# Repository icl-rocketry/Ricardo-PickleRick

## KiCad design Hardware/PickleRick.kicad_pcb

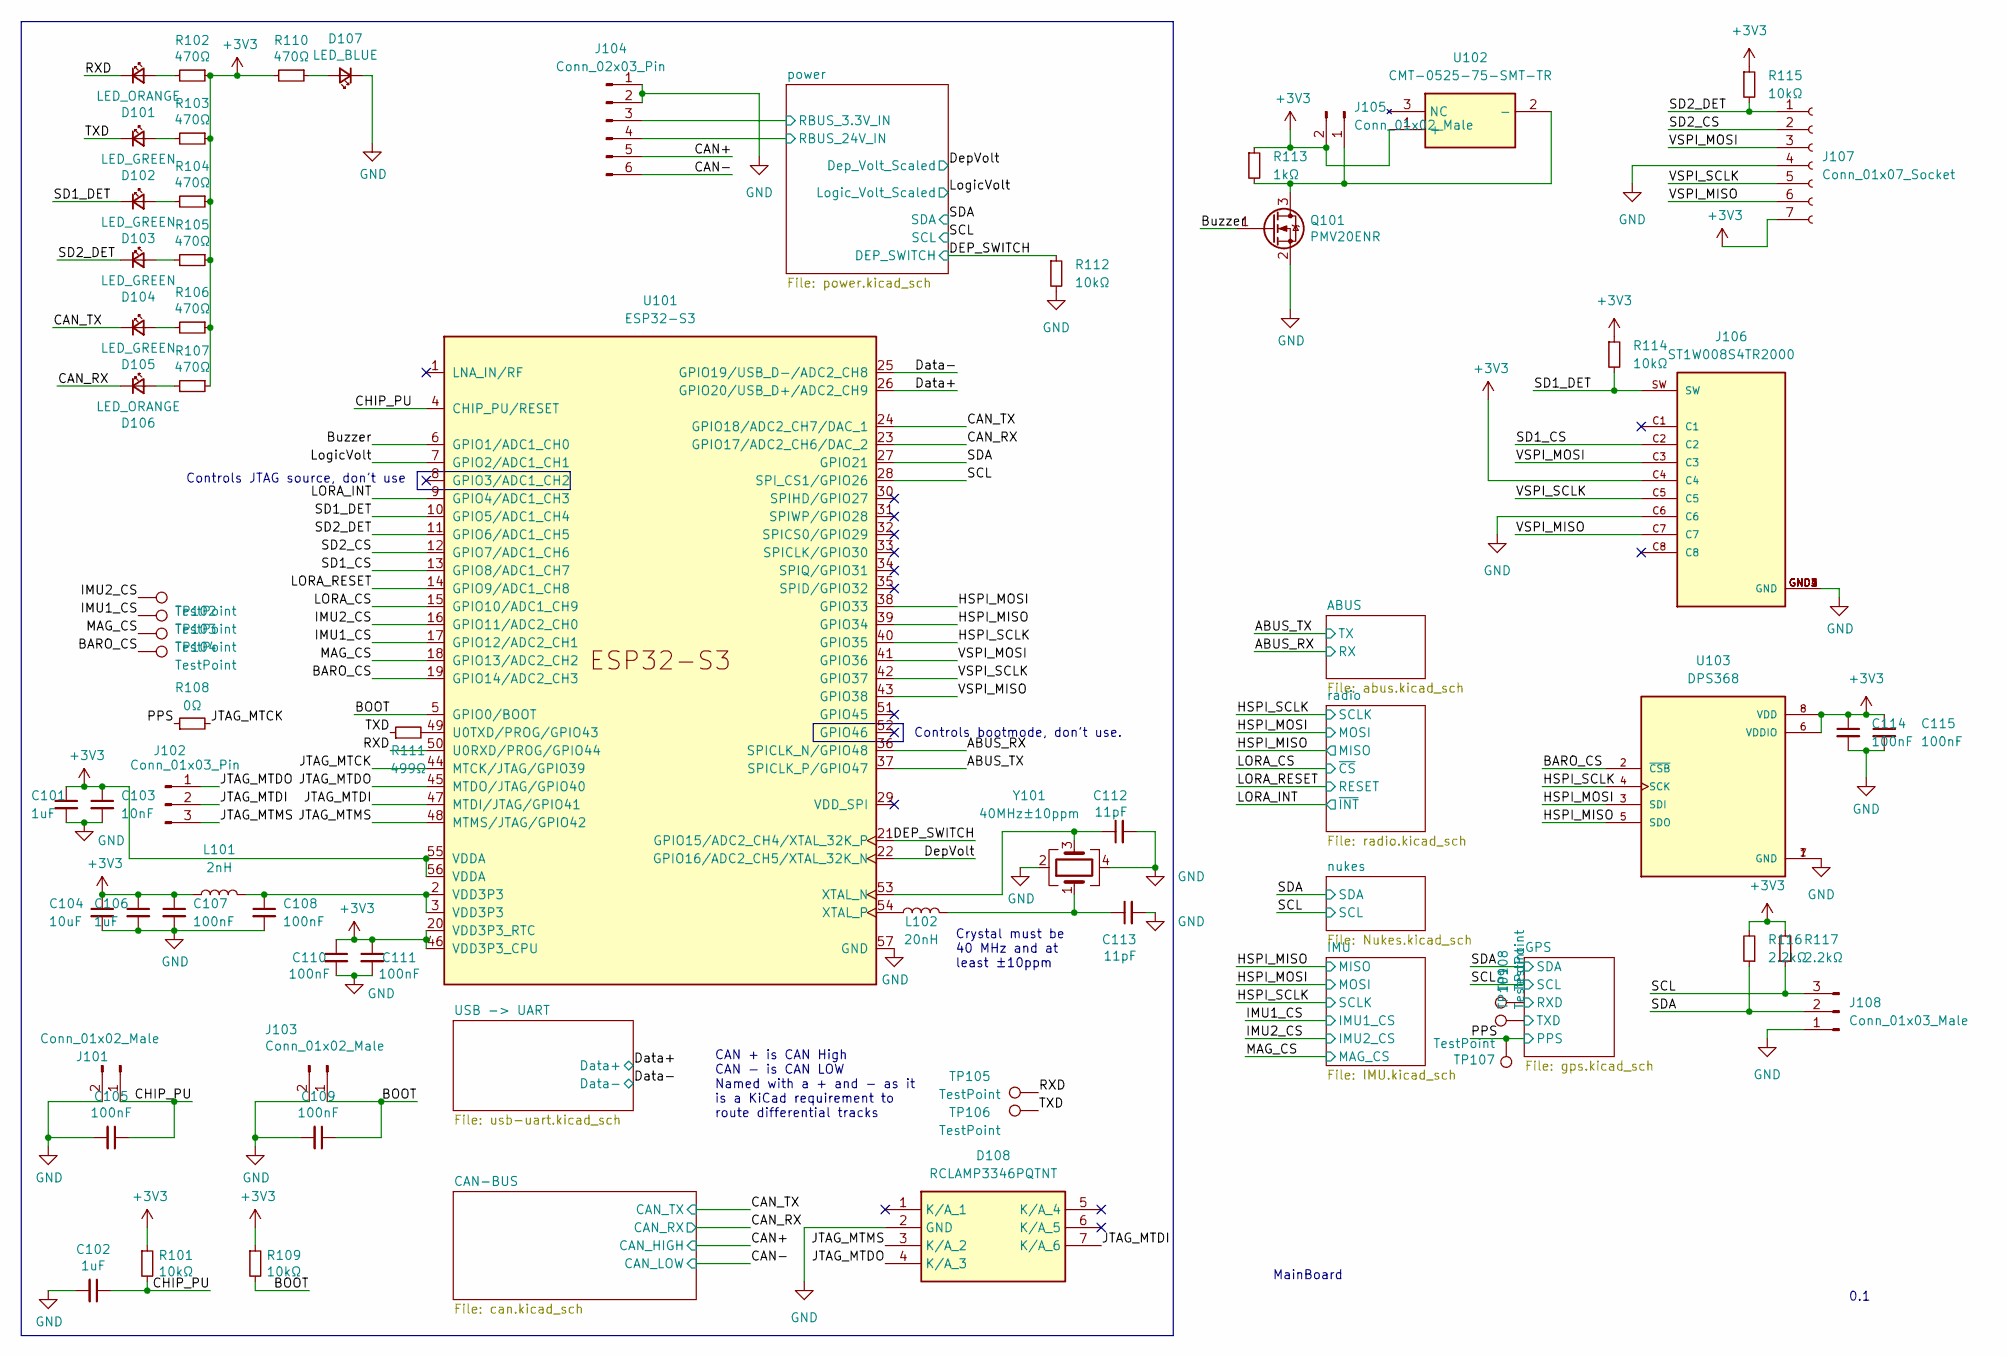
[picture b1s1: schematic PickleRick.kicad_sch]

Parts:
C101, C102, C106: 1uF; C_0402_1005Metric
C103: 10nF; C_0402_1005Metric
C104: 10uF; C_0402_1005Metric
C105, C107, C108, C109, C110, C111, C114, C115: 100nF; C_0402_1005Metric
C112, C113: 11pF; C_0402_1005Metric
D101, D106: LED_ORANGE; LED_0402_1005Metric
D102, D103, D104, D105: LED_GREEN; LED_0402_1005Metric
D107: LED_BLUE; LED_0402_1005Metric
D108: RCLAMP3346PQTNT; Mouser Part Number 947-RCLAMP3346PQTNT
J101, J103: Conn_01x02_Male; PinHeader_1x02_P2.54mm_Vertical
J102: Conn_01x03_Pin; PinHeader_1x03_P2.54mm_Vertical
J104: Conn_02x03_Pin; Molex_Mini-Fit_Jr_5566-06A_2x03_P4.20mm_Vertical
J105: Conn_01x02_Male; JST_PH_B2B-PH-K_1x02_P2.00mm_Vertical
J106: ST1W008S4TR2000; JAE_ST1W008S4TR2000; PARTREV 1
J107: Conn_01x07_Socket; Molex_Pico-Clasp_202396-0707_1x07-1MP_P1.00mm_Horizontal
J108: Conn_01x03_Male; PinHeader_1x03_P2.54mm_Vertical
L101: 2nH; L_0402_1005Metric
L102: 20nH; L_0402_1005Metric
Q101: PMV20ENR; SOT-23
R101, R109, R112, R114, R115: 10kΩ; R_0402_1005Metric
R102, R103, R104, R105, R106, R107, R110: 470Ω; R_0402_1005Metric
R108: 0Ω; R_0402_1005Metric
R111: 499Ω; R_0402_1005Metric
R113: 1kΩ; R_0402_1005Metric
R116, R117: 2.2kΩ; R_0402_1005Metric
TP101, TP102, TP103, TP104, TP105, TP106, TP107, TP108, TP109: TestPoint; TestPoint_Pad_D1.0mm
U101: ESP32-S3; QFN40P700X700X90-57N
U102: CMT-0525-75-SMT-TR; CMT052575SMTTR; Manufacturer_Part_Number CMT-0525-75-SMT-TR; Mouser Part Number 490-CMT-0525-75SMTTR
U103: DPS368; XDCR_DPS310
Y101: 40MHz±10ppm; Crystal_SMD_2016-4Pin_2.0x1.6mm; MPN R940000171

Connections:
+3V3: C101.1, C103.1, C104.1, C106.1, C107.1, C110.1, C111.1, C114.1, C115.1, J105.2, J106.C4, J107.7, L101.1, R101.1, R102.1, R103.1, R104.1, R105.1, R106.1, R107.1, R109.1, R110.2, R113.1, R114.1, R115.1, R116.2, R117.2, U101.20 (VDD3P3_RTC), U101.46 (VDD3P3_CPU), U101.55 (VDDA), U101.56 (VDDA), U102.1 (+), U103.6 (VDDIO), U103.8 (VDD); also elsewhere on the board
/ABUS_RX: U101.36 (SPICLK_N/GPIO48); also elsewhere on the board
/ABUS_TX: U101.37 (SPICLK_P/GPIO47); also elsewhere on the board
/BARO_CS: TP104.1, U101.19 (GPIO14/ADC2_CH3), U103.2 (~CSB)
/BOOT: C109.1, J103.1, R109.2, U101.5 (GPIO0/BOOT)
/Buzzer: Q101.1 (G), U101.6 (GPIO1/ADC1_CH0)
/CAN+: J104.5; also elsewhere on the board
/CAN-: J104.6; also elsewhere on the board
/CAN_RX: D106.1 (K), U101.23 (GPIO17/ADC2_CH6/DAC_2); also elsewhere on the board
/CAN_TX: D105.1 (K), U101.24 (GPIO18/ADC2_CH7/DAC_1); also elsewhere on the board
/CHIP_PU: C102.1, C105.1, J101.1, R101.2, U101.4 (CHIP_PU/RESET)
/DEP_SWITCH: R112.1, U101.21 (GPIO15/ADC2_CH4/XTAL_32K_P); also elsewhere on the board
/Data+: U101.26 (GPIO20/USB_D+/ADC2_CH9); also elsewhere on the board
/Data-: U101.25 (GPIO19/USB_D-/ADC2_CH8); also elsewhere on the board
/DepVolt: U101.22 (GPIO16/ADC2_CH5/XTAL_32K_N); also elsewhere on the board
/GPS/RXD: TP108.1; also elsewhere on the board
/GPS/TXD: TP109.1; also elsewhere on the board
/HSPI_MISO: U101.39 (GPIO34), U103.5 (SDO); also elsewhere on the board
/HSPI_MOSI: U101.38 (GPIO33), U103.3 (SDI); also elsewhere on the board
/HSPI_SCLK: U101.40 (GPIO35), U103.4 (SCK); also elsewhere on the board
/IMU1_CS: TP102.1, U101.17 (GPIO12/ADC2_CH1); also elsewhere on the board
/IMU2_CS: TP101.1, U101.16 (GPIO11/ADC2_CH0); also elsewhere on the board
/JTAG_MTCK: R108.2, U101.44 (MTCK/JTAG/GPIO39)
/JTAG_MTDI: D108.7 (K/A_6), J102.2, U101.47 (MTDI/JTAG/GPIO41)
/JTAG_MTDO: D108.4 (K/A_3), J102.1, U101.45 (MTDO/JTAG/GPIO40)
/JTAG_MTMS: D108.3 (K/A_2), J102.3, U101.48 (MTMS/JTAG/GPIO42)
/LORA_CS: U101.15 (GPIO10/ADC1_CH9); also elsewhere on the board
/LORA_INT: U101.9 (GPIO4/ADC1_CH3); also elsewhere on the board
/LORA_RESET: U101.14 (GPIO9/ADC1_CH8); also elsewhere on the board
/LogicVolt: U101.7 (GPIO2/ADC1_CH1); also elsewhere on the board
/MAG_CS: TP103.1, U101.18 (GPIO13/ADC2_CH2); also elsewhere on the board
/PPS: R108.1, TP107.1; also elsewhere on the board
/RXD: D101.1 (K), TP105.1, U101.50 (U0RXD/PROG/GPIO44)
/SCL: J108.3, R117.1, U101.28 (SPI_CS1/GPIO26); also elsewhere on the board
/SD1_CS: J106.C2, U101.13 (GPIO8/ADC1_CH7)
/SD1_DET: D103.1 (K), J106.SW, R114.2, U101.10 (GPIO5/ADC1_CH4)
/SD2_CS: J107.2, U101.12 (GPIO7/ADC1_CH6)
/SD2_DET: D104.1 (K), J107.1, R115.2, U101.11 (GPIO6/ADC1_CH5)
/SDA: J108.2, R116.1, U101.27 (GPIO21); also elsewhere on the board
/TXD: D102.1 (K), R111.1, TP106.1
/VSPI_MISO: J106.C7, J107.6, U101.43 (GPIO38)
/VSPI_MOSI: J106.C3, J107.3, U101.41 (GPIO36)
/VSPI_SCLK: J106.C5, J107.5, U101.42 (GPIO37)
/power/RBUS_3.3V_IN: J104.3; also elsewhere on the board
/power/RBUS_24V_IN: J104.4; also elsewhere on the board
GND: C101.2, C102.2, C103.2, C104.2, C105.2, C106.2, C107.2, C108.2, C109.2, C110.2, C111.2, C112.2, C113.2, C114.2, C115.2, D107.1 (K), D108.2 (GND), J101.2, J103.2, J104.1, J104.2, J106.C6, J106.GND1 (GND), J106.GND2 (GND), J106.GND3 (GND), J106.GND4 (GND), J107.4, J108.1, Q101.2 (S), R112.2, U101.57 (GND), U103.1 (GND), U103.7 (GND), Y101.2, Y101.4; also elsewhere on the board
unnamed: C108.1, L101.2, U101.2 (VDD3P3), U101.3 (VDD3P3)
unnamed: C113.1, L102.2, Y101.1
unnamed: D101.2 (A), R102.2
unnamed: D102.2 (A), R103.2
unnamed: D103.2 (A), R104.2
unnamed: D104.2 (A), R105.2
unnamed: D105.2 (A), R106.2
unnamed: D106.2 (A), R107.2
unnamed: D107.2 (A), R110.1
unnamed: J105.1, Q101.3 (D), R113.2, U102.2 (-)
unnamed: R111.2, U101.49 (U0TXD/PROG/GPIO43)
unnamed: C112.1, U101.53 (XTAL_N), Y101.3
unnamed: L102.1, U101.54 (XTAL_P)

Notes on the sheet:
Controls JTAG source, don't use
CAN + is CAN High CAN - is CAN LOW Named with a + and - as it is a KiCad requirement to route differential tracks
MainBoard
Controls bootmode, don't use.
0.1
Crystal must be 40 MHz and at least ±10ppm

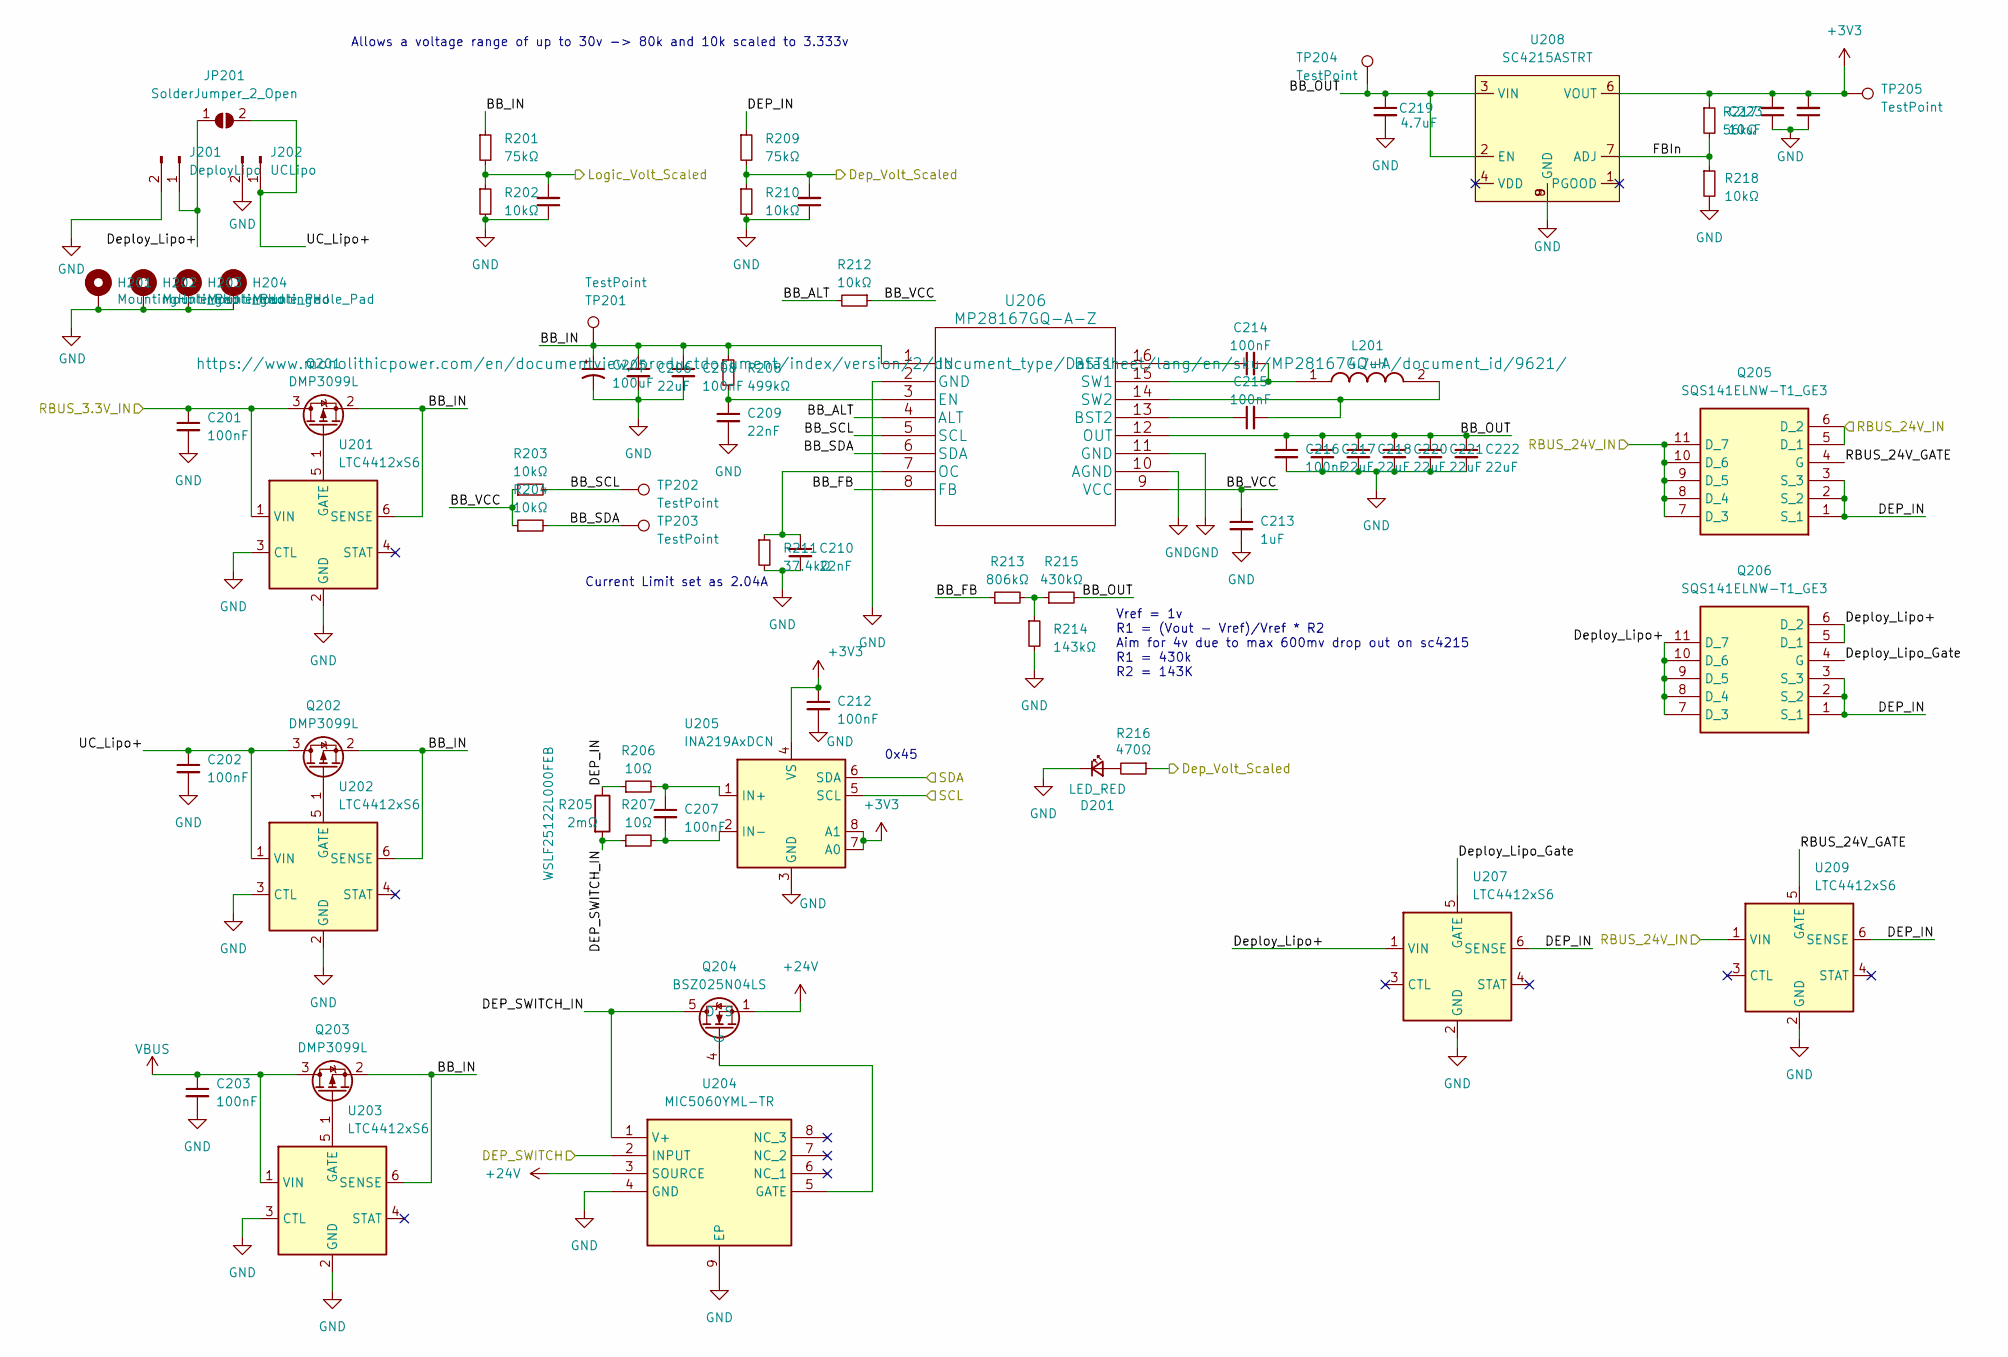
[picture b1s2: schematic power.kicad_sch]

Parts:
C201, C202, C203, C204, C207, C208, C211, C212, C214, C215, C216, C224: 100nF; C_0402_1005Metric
C205: 100uF; CP_Elec_6.3x9.9
C206: 22uF; C_0805_2012Metric
C209, C210: 22nF; C_0402_1005Metric
C213: 1uF; C_0402_1005Metric
C217, C218, C220, C221, C222: 22uF; C_0402_1005Metric
C219: 4.7uF; C_0402_1005Metric
C223: 10uF; C_0402_1005Metric
D201: LED_RED; LED_0402_1005Metric
H201, H202, H203, H204: MountingHole_Pad; MountingHole_3.2mm_M3_DIN965_Pad
J201: DeployLipo; TerminalBlock_Phoenix_MKDS-3-2-5.08_1x02_P5.08mm_Horizontal
J202: UCLipo; JST_PH_B2B-PH-K_1x02_P2.00mm_Vertical
JP201: SolderJumper_2_Open; SolderJumper-2_P1.3mm_Open_RoundedPad1.0x1.5mm
L201: 4.7uH; MPLAL60504R7; Manufacturer_Part_Number MPL-AL6050-4R7; Mouser Part Number 946-MPL-AL6050-4R7
Q201, Q202, Q203: DMP3099L; SOT-23
Q204: BSZ025N04LS; Manufacturer_Part_Number BSZ025N04LS; Mouser Part Number 726-BSZ025N04LS
Q205, Q206: SQS141ELNW-T1_GE3; SQS850ENT1_GE3; Manufacturer_Part_Number SQS141ELNW-T1_GE3; Mouser Part Number 78-SQS141ELNW-T1_GE3
R201, R209: 75kΩ; R_0402_1005Metric
R202, R203, R204, R210, R212, R218: 10kΩ; R_0402_1005Metric
R205: 2mΩ; R_2512_6332Metric_Pad1.40x3.35mm_HandSolder; Part Number WSLF25122L000FEB
R206, R207: 10Ω; R_0402_1005Metric
R208: 499kΩ; R_0402_1005Metric
R211: 37.4kΩ; R_0402_1005Metric
R213: 806kΩ; R_0402_1005Metric
R214: 143kΩ; R_0402_1005Metric
R215: 430kΩ; R_0402_1005Metric
R216: 470Ω; R_0402_1005Metric
R217: 56kΩ; R_0402_1005Metric
TP201, TP204, TP205: TestPoint; TestPoint_Pad_D2.0mm
TP202, TP203: TestPoint; TestPoint_Pad_D1.0mm
U201, U202, U203, U207, U209: LTC4412xS6; TSOT-23-6
U204: MIC5060YML-TR; SON65P300X300X100-9N-D; Manufacturer_Part_Number MIC5060YML-TR; Mouser Part Number 998-MIC5060YMLTR
U205: INA219AxDCN; SOT-23-8
U206: MP28167GQ-A-Z
U208: SC4215ASTRT; SOIC127P599X175-9N

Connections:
+3V3: C212.1, C223.2, C224.2, R217.1, TP205.1, U205.4 (VS), U205.7 (A0), U205.8 (A1), U208.6 (VOUT); also elsewhere on the board
+24V: Q204.1 (S), Q204.2 (S), Q204.3 (S), Q204.A1 (S), U204.3 (SOURCE); also elsewhere on the board
/DEP_SWITCH: U204.2 (INPUT); also elsewhere on the board
/DepVolt: C211.2, R209.2, R210.1, R216.1; also elsewhere on the board
/LogicVolt: C204.2, R201.2, R202.1; also elsewhere on the board
/SCL: U205.5 (SCL); also elsewhere on the board
/SDA: U205.6 (SDA); also elsewhere on the board
/power/BB_ALT: R212.2, U206.4 (ALT)
/power/BB_FB: R213.1, U206.8 (FB)
/power/BB_IN: C205.1, C206.1, C208.1, Q201.2 (S), Q202.2 (S), Q203.2 (S), R201.1, R208.1, TP201.1, U201.6 (SENSE), U202.6 (SENSE), U203.6 (SENSE), U206.1 (IN)
/power/BB_OUT: C216.1, C217.1, C218.1, C219.1, C220.1, C221.1, C222.1, R215.2, TP204.1, U206.12 (OUT), U208.2 (EN), U208.3 (VIN)
/power/BB_SCL: R203.2, TP202.1, U206.5 (SCL)
/power/BB_SDA: R204.2, TP203.1, U206.6 (SDA)
/power/BB_VCC: C213.1, R203.1, R204.1, R212.1, U206.9 (VCC)
/power/DEP_IN: Q205.1 (S_1), Q205.2 (S_2), Q205.3 (S_3), Q206.1 (S_1), Q206.2 (S_2), Q206.3 (S_3), R205.1, R206.1, R209.1, U207.6 (SENSE), U209.6 (SENSE)
/power/DEP_SWITCH_IN: Q204.5 (D), Q204.6 (D), Q204.7 (D), Q204.8 (D), Q204.A5 (D), R205.2, R207.1, U204.1 (V+)
/power/Deploy_Lipo+: J201.1, JP201.1 (A), Q206.5 (D_1), Q206.6 (D_2), Q206.7 (D_3), Q206.8 (D_4), Q206.9 (D_5), Q206.10 (D_6), Q206.11 (D_7), U207.1 (VIN)
/power/Deploy_Lipo_Gate: Q206.4 (G), U207.5 (GATE)
/power/FBIn: R217.2, R218.1, U208.7 (ADJ)
/power/RBUS_3.3V_IN: C201.1, Q201.3 (D), U201.1 (VIN); also elsewhere on the board
/power/RBUS_24V_GATE: Q205.4 (G), U209.5 (GATE)
/power/RBUS_24V_IN: Q205.5 (D_1), Q205.6 (D_2), Q205.7 (D_3), Q205.8 (D_4), Q205.9 (D_5), Q205.10 (D_6), Q205.11 (D_7), U209.1 (VIN); also elsewhere on the board
/power/UC_Lipo+: C202.1, J202.1, JP201.2 (B), Q202.3 (D), U202.1 (VIN)
GND: C201.2, C202.2, C203.2, C204.1, C205.2, C206.2, C208.2, C209.2, C210.2, C211.1, C212.2, C213.2, C216.2, C217.2, C218.2, C219.2, C220.2, C221.2, C222.2, C223.1, C224.1, D201.1 (K), H201.1, H202.1, H203.1, H204.1, J201.2, J202.2, R202.2, R210.2, R211.2, R214.2, R218.2, U201.2 (GND), U201.3 (CTL), U202.2 (GND), U202.3 (CTL), U203.2 (GND), U203.3 (CTL), U204.4 (GND), U204.9 (EP), U205.3 (GND), U206.2 (GND), U206.10 (AGND), U206.11 (GND), U207.2 (GND), U208.8 (GND), U208.9 (GND), U209.2 (GND); also elsewhere on the board
unnamed: D201.2 (A), R216.2
unnamed: Q201.1 (G), U201.5 (GATE)
unnamed: Q202.1 (G), U202.5 (GATE)
unnamed: Q203.1 (G), U203.5 (GATE)
unnamed: Q204.4 (G), U204.5 (GATE)
unnamed: R213.2, R214.1, R215.1
unnamed: C207.1, R206.2, U205.1 (IN+)
unnamed: C207.2, R207.2, U205.2 (IN-)
unnamed: C214.1, U206.16 (BST1)
unnamed: C215.1, U206.13 (BST2)
unnamed: C209.1, R208.2, U206.3 (EN)
unnamed: C210.1, R211.1, U206.7 (OC)
unnamed: C214.2, L201.1, U206.15 (SW1)
unnamed: C215.2, L201.2, U206.14 (SW2)
VBUS: C203.1, Q203.3 (D), U203.1 (VIN); also elsewhere on the board

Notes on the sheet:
0x45
Allows a voltage range of up to 30v -> 80k and 10k scaled to 3.333v
Vref = 1v R1 = (Vout - Vref)/Vref * R2 Aim for 4v due to max 600mv drop out on sc4215 R1 = 430k R2 = 143K
Current Limit set as 2.04A

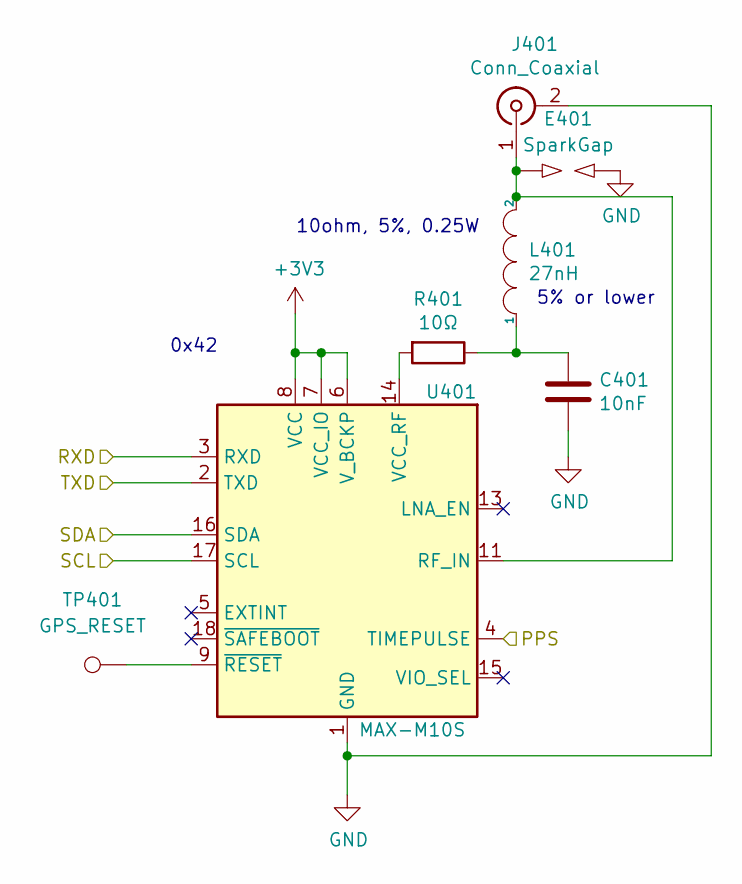
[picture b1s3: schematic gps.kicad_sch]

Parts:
C401: 10nF; C_0402_1005Metric
E401: SparkGap; Spark_Gap
J401: Conn_Coaxial; SMA_Molex_73251-1153_EdgeMount_Horizontal
L401: 27nH; L_0402_1005Metric; Part LQG15HZ27NH02D
R401: 10Ω; R_0603_1608Metric
TP401: GPS_RESET; TestPoint_Pad_D1.0mm
U401: MAX-M10S; ublox_MAX

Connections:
+3V3: U401.6 (V_BCKP), U401.7 (VCC_IO), U401.8 (VCC); also elsewhere on the board
/GPS/RXD: U401.3 (RXD); also elsewhere on the board
/GPS/TXD: U401.2 (TXD); also elsewhere on the board
/PPS: U401.4 (TIMEPULSE); also elsewhere on the board
/SCL: U401.17 (SCL); also elsewhere on the board
/SDA: U401.16 (SDA); also elsewhere on the board
GND: C401.2, E401.2, J401.2 (Ext), U401.1 (GND), U401.10 (GND), U401.12 (GND); also elsewhere on the board
unnamed: C401.1, L401.1, R401.1
unnamed: E401.1, J401.1 (In), L401.2, U401.11 (RF_IN)
unnamed: R401.2, U401.14 (VCC_RF)
unnamed: TP401.1, U401.9 (~RESET)

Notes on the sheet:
5% or lower
0x42
10ohm, 5%, 0.25W

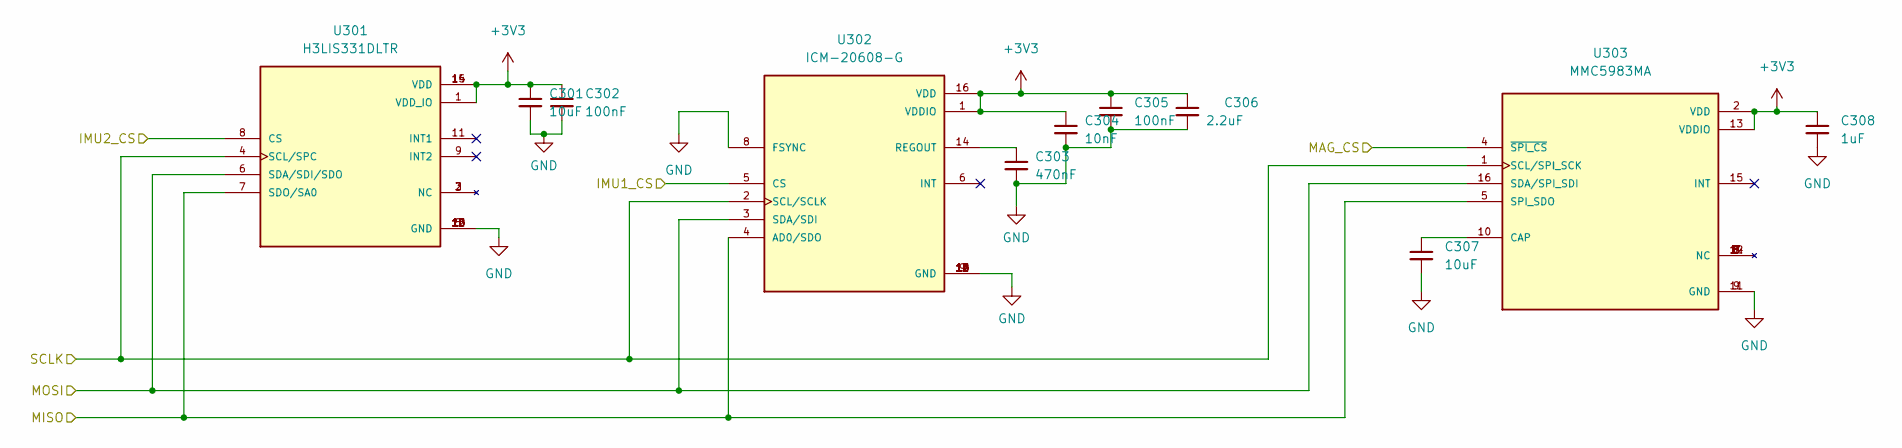
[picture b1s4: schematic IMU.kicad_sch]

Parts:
C301, C307: 10uF; C_0402_1005Metric
C302, C305: 100nF; C_0402_1005Metric
C303: 470nF; C_0402_1005Metric
C304: 10nF; C_0402_1005Metric
C306: 2.2uF; C_0402_1005Metric
C308: 1uF; C_0402_1005Metric
U301: H3LIS331DLTR; QFN300X300X100-16N; PARTREV 2
U302: ICM-20608-G; PQFN50P300X300X80-16N; PARTREV 1.0
U303: MMC5983MA; PQFN50P300X300X100-16N; PARTREV A

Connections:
+3V3: C301.1, C302.1, C304.1, C305.1, C306.1, C308.1, U301.1 (VDD_IO), U301.14 (VDD), U301.15 (VDD), U302.1 (VDDIO), U302.16 (VDD), U303.2 (VDD), U303.13 (VDDIO); also elsewhere on the board
/HSPI_MISO: U301.7 (SDO/SA0), U302.4 (AD0/SDO), U303.5 (SPI_SDO); also elsewhere on the board
/HSPI_MOSI: U301.6 (SDA/SDI/SDO), U302.3 (SDA/SDI), U303.16 (SDA/SPI_SDI); also elsewhere on the board
/HSPI_SCLK: U301.4 (SCL/SPC), U302.2 (SCL/SCLK), U303.1 (SCL/SPI_SCK); also elsewhere on the board
/IMU1_CS: U302.5 (CS); also elsewhere on the board
/IMU2_CS: U301.8 (CS); also elsewhere on the board
/MAG_CS: U303.4 (~SPI_CS); also elsewhere on the board
GND: C301.2, C302.2, C303.2, C304.2, C305.2, C306.2, C307.2, C308.2, U301.5 (GND), U301.10 (GND), U301.12 (GND), U301.13 (GND), U301.16 (GND), U302.8 (FSYNC), U302.9 (GND), U302.10 (GND), U302.11 (GND), U302.12 (GND), U302.13 (GND), U302.15 (GND), U303.9 (GND), U303.11 (GND); also elsewhere on the board
unnamed: C303.1, U302.14 (REGOUT)
unnamed: C307.1, U303.10 (CAP)

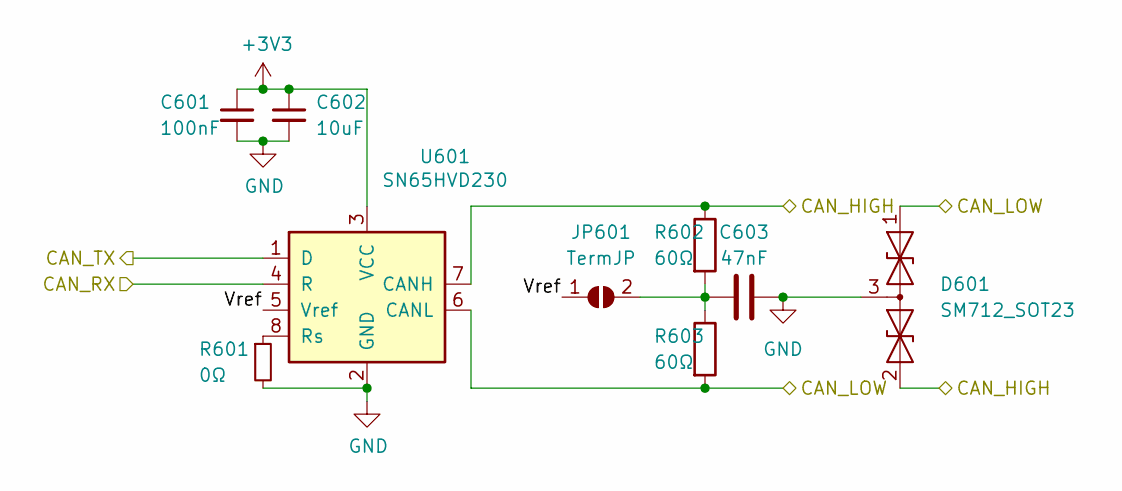
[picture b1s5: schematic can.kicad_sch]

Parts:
C601: 100nF; C_0402_1005Metric
C602: 10uF; C_0402_1005Metric
C603: 47nF; C_0402_1005Metric
D601: SM712_SOT23; SOT-23
JP601: TermJP; SmallerSolderJP
R601: 0Ω; R_0603_1608Metric
R602, R603: 60Ω; R_0603_1608Metric
U601: SN65HVD230; SOIC-8_3.9x4.9mm_P1.27mm

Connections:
+3V3: C601.1, C602.1, U601.3 (VCC); also elsewhere on the board
/CAN+: D601.2 (A2), R602.1, U601.7 (CANH); also elsewhere on the board
/CAN-: D601.1 (A1), R603.2, U601.6 (CANL); also elsewhere on the board
/CAN-BUS/Vref: JP601.1 (A), U601.5 (Vref)
/CAN_RX: U601.4 (R); also elsewhere on the board
/CAN_TX: U601.1 (D); also elsewhere on the board
GND: C601.2, C602.2, C603.2, D601.3 (common), R601.2, U601.2 (GND); also elsewhere on the board
unnamed: C603.1, JP601.2 (B), R602.2, R603.1
unnamed: R601.1, U601.8 (Rs)

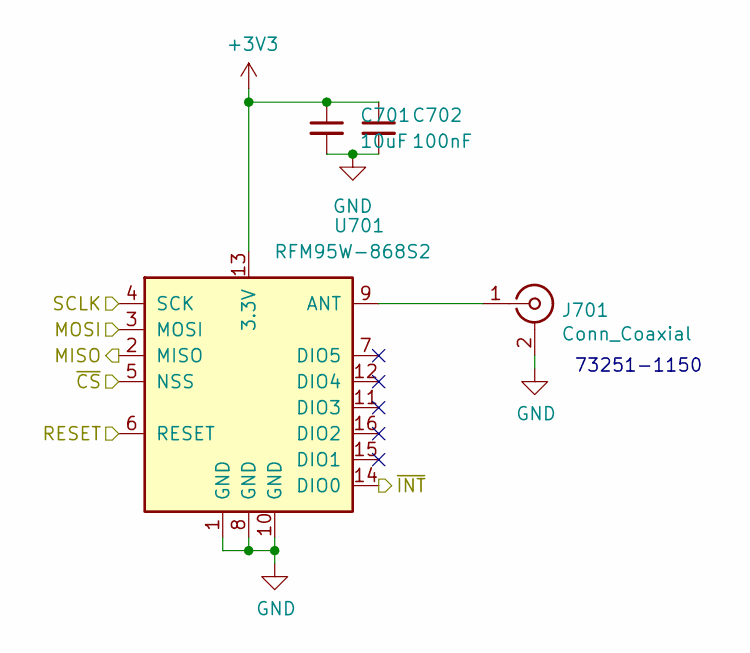
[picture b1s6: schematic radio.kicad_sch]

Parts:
C701: 10uF; C_0402_1005Metric
C702: 100nF; C_0402_1005Metric
J701: Conn_Coaxial; SMA_Molex_73251-1153_EdgeMount_Horizontal
U701: RFM95W-868S2; HOPERF_RFM9XW_SMD

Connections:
+3V3: C701.1, C702.1, U701.13 (3.3V); also elsewhere on the board
/HSPI_MISO: U701.2 (MISO); also elsewhere on the board
/HSPI_MOSI: U701.3 (MOSI); also elsewhere on the board
/HSPI_SCLK: U701.4 (SCK); also elsewhere on the board
/LORA_CS: U701.5 (NSS); also elsewhere on the board
/LORA_INT: U701.14 (DIO0); also elsewhere on the board
/LORA_RESET: U701.6 (RESET); also elsewhere on the board
GND: C701.2, C702.2, J701.2 (Ext), U701.1 (GND), U701.8 (GND), U701.10 (GND); also elsewhere on the board
unnamed: J701.1 (In), U701.9 (ANT)

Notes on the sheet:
73251-1150

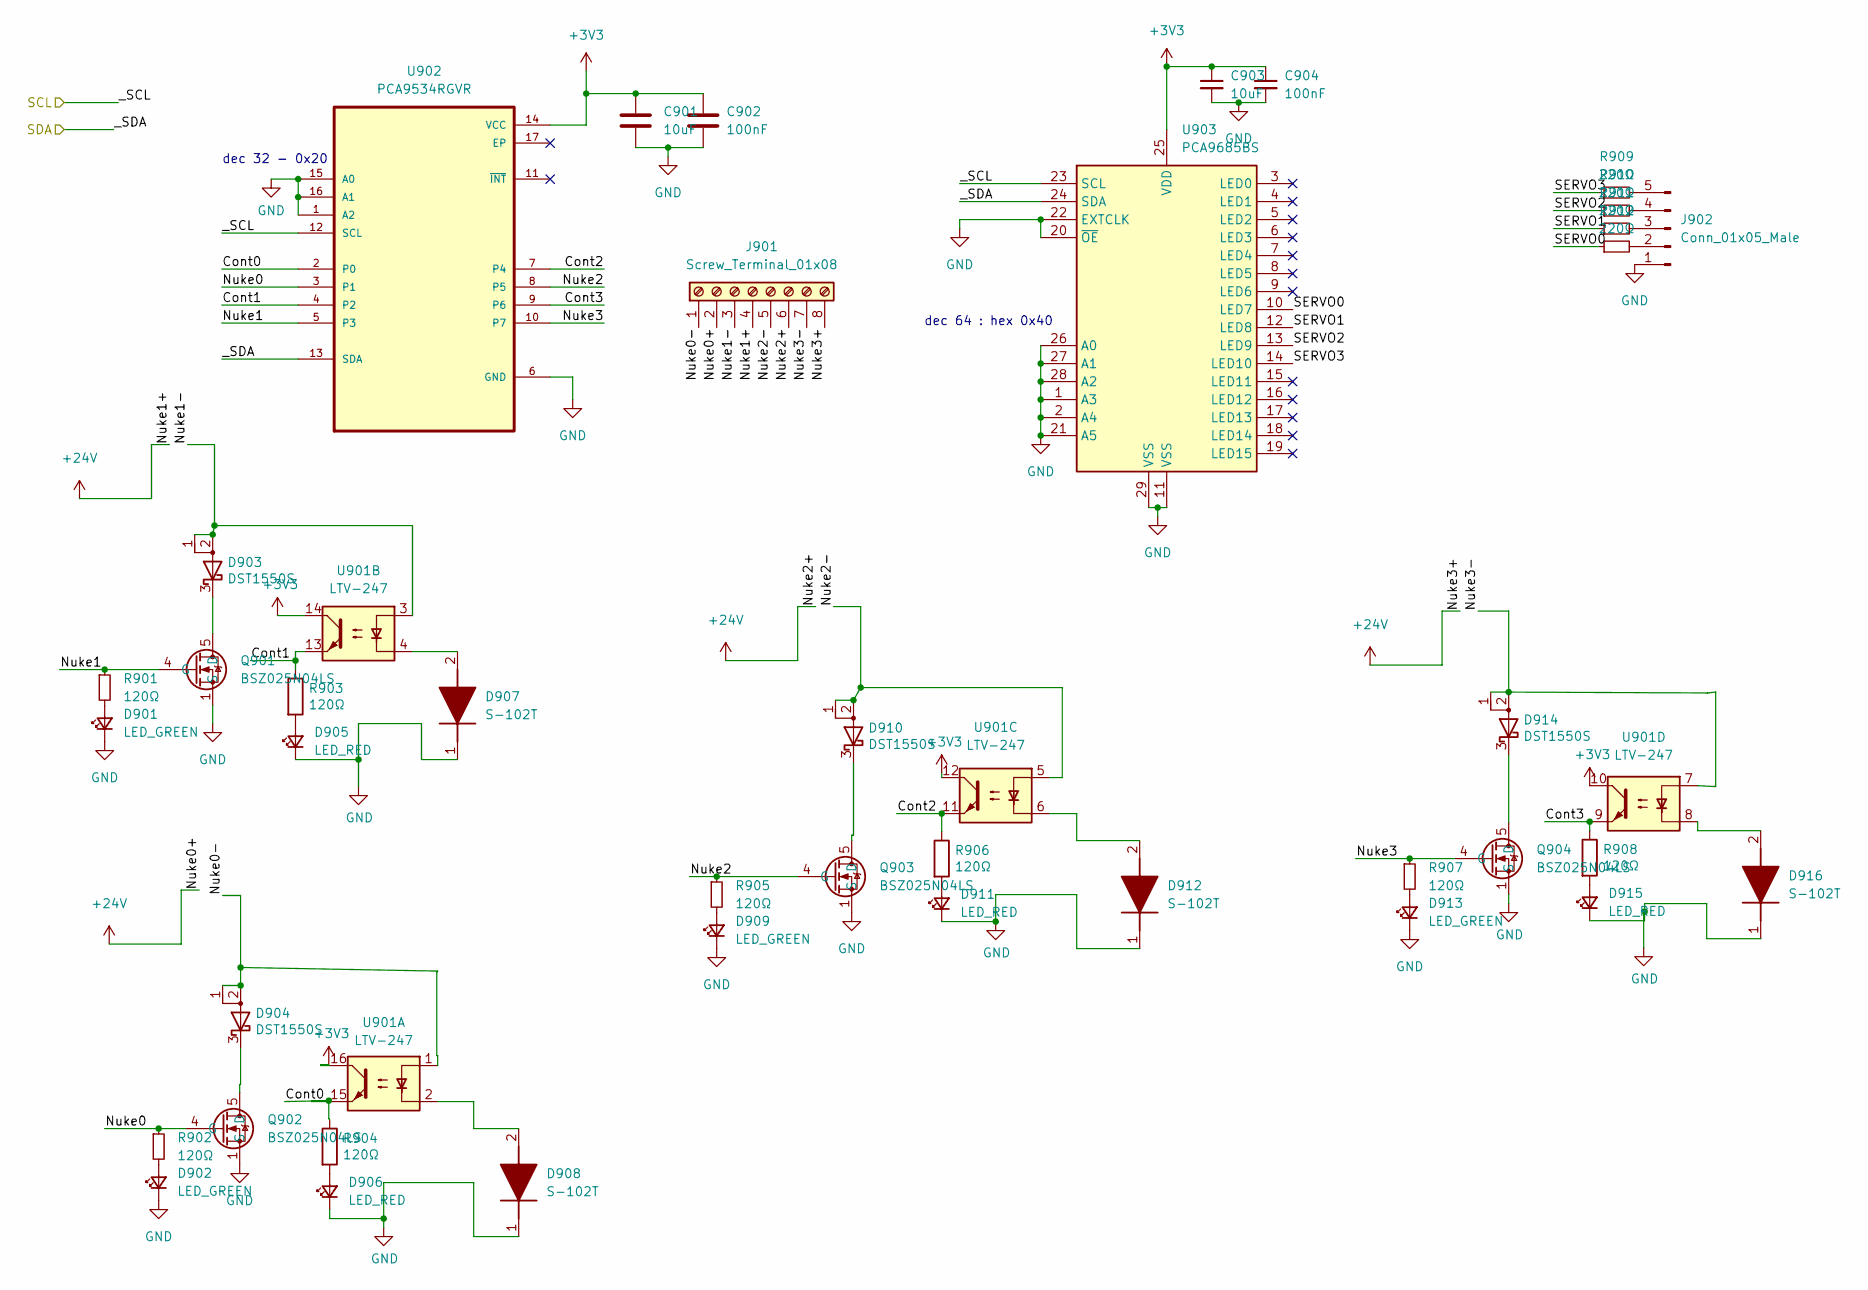
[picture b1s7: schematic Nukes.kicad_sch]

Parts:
C901, C903: 10uF; C_0402_1005Metric
C902, C904: 100nF; C_0402_1005Metric
D901, D902, D909, D913: LED_GREEN; LED_0402_1005Metric
D903, D904, D910, D914: DST1550S; TO-277B
D905, D906, D911, D915: LED_RED; LED_0402_1005Metric
D907, D908, D912, D916: S-102T; SODFL3516X70N; Manufacturer_Part_Number S-102T; Mouser Part Number 954-S-102T
J901: Screw_Terminal_01x08; TerminalBlock_TE_282834-8_1x08_P2.54mm_Horizontal
J902: Conn_01x05_Male; PinHeader_1x05_P2.54mm_Vertical
Q901, Q902, Q903, Q904: BSZ025N04LS; Manufacturer_Part_Number BSZ025N04LS; Mouser Part Number 726-BSZ025N04LS
R901, R902, R903, R904, R905, R906, R907, R908: 120Ω; R_0402_1005Metric
R909, R910, R911, R912: 220Ω; R_0402_1005Metric
U901: LTV-247; SOP-16_4.4x10.4mm_P1.27mm
U902: PCA9534RGVR; QFN65P400X400X100-17N
U903: PCA9685BS; QFN-28-1EP_6x6mm_P0.65mm_EP4.25x4.25mm

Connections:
+3V3: C901.1, C902.1, C903.1, C904.1, U901.10, U901.12, U901.14, U901.16, U902.14 (VCC), U903.25 (VDD); also elsewhere on the board
+24V: J901.2, J901.4, J901.6, J901.8; also elsewhere on the board
/SCL: U902.12 (SCL), U903.23 (SCL); also elsewhere on the board
/SDA: U902.13 (SDA), U903.24 (SDA); also elsewhere on the board
/nukes/Cont0: R904.1, U901.15, U902.2 (P0)
/nukes/Cont1: R903.1, U901.13, U902.4 (P2)
/nukes/Cont2: R906.1, U901.11, U902.7 (P4)
/nukes/Cont3: R908.1, U901.9, U902.9 (P6)
/nukes/Nuke0: Q902.4 (G), R902.1, U902.3 (P1)
/nukes/Nuke0-: D904.1 (A), D904.2 (A), J901.1, U901.1
/nukes/Nuke1: Q901.4 (G), R901.1, U902.5 (P3)
/nukes/Nuke1-: D903.1 (A), D903.2 (A), J901.3, U901.3
/nukes/Nuke2: Q903.4 (G), R905.1, U902.8 (P5)
/nukes/Nuke2-: D910.1 (A), D910.2 (A), J901.5, U901.5
/nukes/Nuke3: Q904.4 (G), R907.1, U902.10 (P7)
/nukes/Nuke3-: D914.1 (A), D914.2 (A), J901.7, U901.7
/nukes/SERVO0: R912.1, U903.10 (LED7)
/nukes/SERVO1: R911.1, U903.12 (LED8)
/nukes/SERVO2: R910.1, U903.13 (LED9)
/nukes/SERVO3: R909.1, U903.14 (LED10)
GND: C901.2, C902.2, C903.2, C904.2, D901.1 (K), D902.1 (K), D905.1 (K), D906.1 (K), D907.1 (K), D908.1 (K), D909.1 (K), D911.1 (K), D912.1 (K), D913.1 (K), D915.1 (K), D916.1 (K), J902.1, Q901.1 (S), Q901.2 (S), Q901.3 (S), Q901.A1 (S), Q902.1 (S), Q902.2 (S), Q902.3 (S), Q902.A1 (S), Q903.1 (S), Q903.2 (S), Q903.3 (S), Q903.A1 (S), Q904.1 (S), Q904.2 (S), Q904.3 (S), Q904.A1 (S), U902.1 (A2), U902.6 (GND), U902.15 (A0), U902.16 (A1), U903.1 (A3), U903.2 (A4), U903.11 (VSS), U903.20 (~OE), U903.21 (A5), U903.22 (EXTCLK), U903.26 (A0), U903.27 (A1), U903.28 (A2), U903.29 (VSS); also elsewhere on the board
unnamed: D901.2 (A), R901.2
unnamed: D902.2 (A), R902.2
unnamed: D903.3 (K), Q901.5 (D), Q901.6 (D), Q901.7 (D), Q901.8 (D), Q901.A5 (D)
unnamed: D904.3 (K), Q902.5 (D), Q902.6 (D), Q902.7 (D), Q902.8 (D), Q902.A5 (D)
unnamed: D905.2 (A), R903.2
unnamed: D906.2 (A), R904.2
unnamed: D907.2 (A), U901.4
unnamed: D908.2 (A), U901.2
unnamed: D909.2 (A), R905.2
unnamed: D910.3 (K), Q903.5 (D), Q903.6 (D), Q903.7 (D), Q903.8 (D), Q903.A5 (D)
unnamed: D911.2 (A), R906.2
unnamed: D912.2 (A), U901.6
unnamed: D913.2 (A), R907.2
unnamed: D914.3 (K), Q904.5 (D), Q904.6 (D), Q904.7 (D), Q904.8 (D), Q904.A5 (D)
unnamed: D915.2 (A), R908.2
unnamed: D916.2 (A), U901.8
unnamed: J902.2, R912.2
unnamed: J902.3, R911.2
unnamed: J902.4, R910.2
unnamed: J902.5, R909.2

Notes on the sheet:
dec 32 - 0x20
dec 64 : hex 0x40

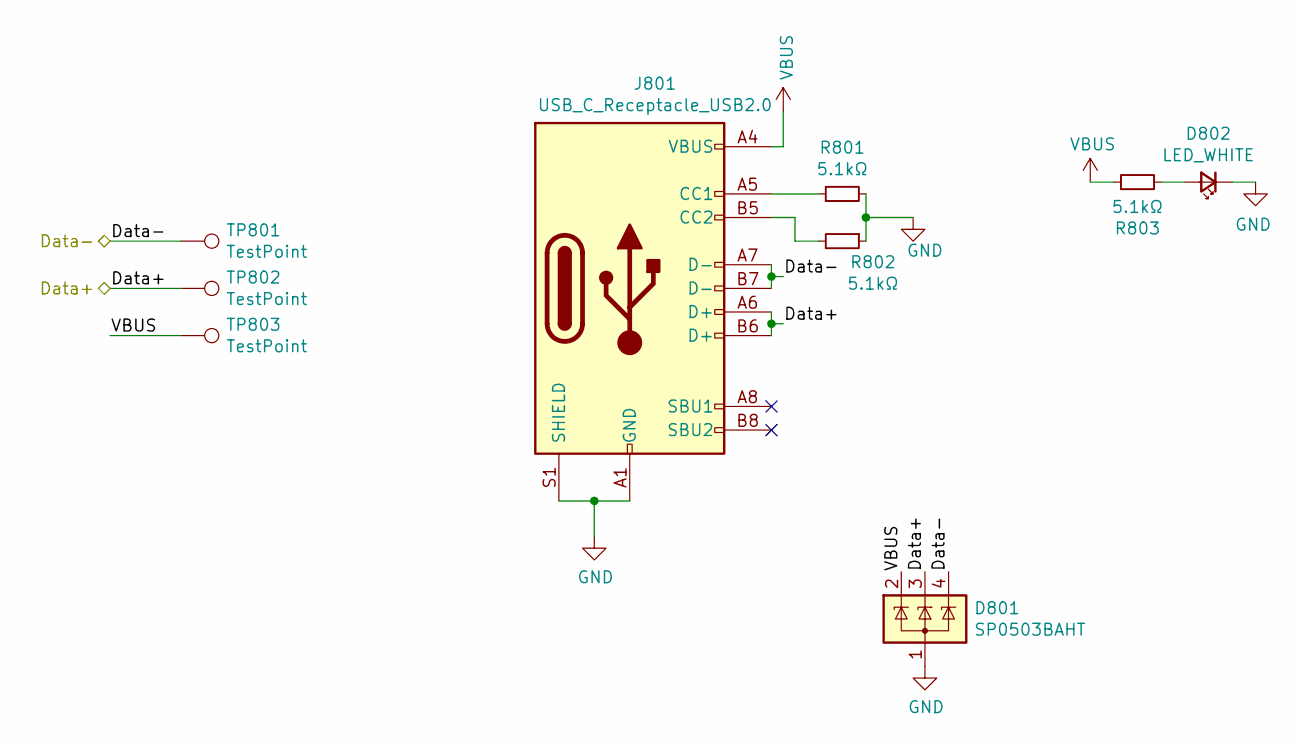
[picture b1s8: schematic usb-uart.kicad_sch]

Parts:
D801: SP0503BAHT; SOT-143
D802: LED_WHITE; LED_0402_1005Metric
J801: USB_C_Receptacle_USB2.0; USB_C_Receptacle_Palconn_UTC16-G
R801, R802, R803: 5.1kΩ; R_0402_1005Metric
TP801, TP802, TP803: TestPoint; TestPoint_Pad_D1.0mm

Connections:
/Data+: D801.3 (K), J801.A6 (D+), J801.B6 (D+), TP802.1; also elsewhere on the board
/Data-: D801.4 (K), J801.A7 (D-), J801.B7 (D-), TP801.1; also elsewhere on the board
GND: D801.1 (A), D802.1 (K), J801.A1 (GND), J801.A12 (GND), J801.B1 (GND), J801.B12 (GND), J801.S1 (SHIELD), R801.2, R802.1; also elsewhere on the board
unnamed: D802.2 (A), R803.2
unnamed: J801.A5 (CC1), R801.1
unnamed: J801.B5 (CC2), R802.2
VBUS: D801.2 (K), J801.A4 (VBUS), J801.A9 (VBUS), J801.B4 (VBUS), J801.B9 (VBUS), R803.1, TP803.1; also elsewhere on the board

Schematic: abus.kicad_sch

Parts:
D501: CPDV5-3V3UP-HF; SOT-353_SC-70-5
J501: Conn_01x03_Pin; Molex_Nano-Fit_105313-xx03_1x03_P2.50mm_Horizontal

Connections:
/ABUS_RX: D501.5, J501.3; also elsewhere on the board
/ABUS_TX: D501.4, J501.2; also elsewhere on the board
GND: D501.1, D501.3, J501.1; also elsewhere on the board

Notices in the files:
parts and their libraries:
Copyright 2021 Accelerated Designs. All rights reserved.
